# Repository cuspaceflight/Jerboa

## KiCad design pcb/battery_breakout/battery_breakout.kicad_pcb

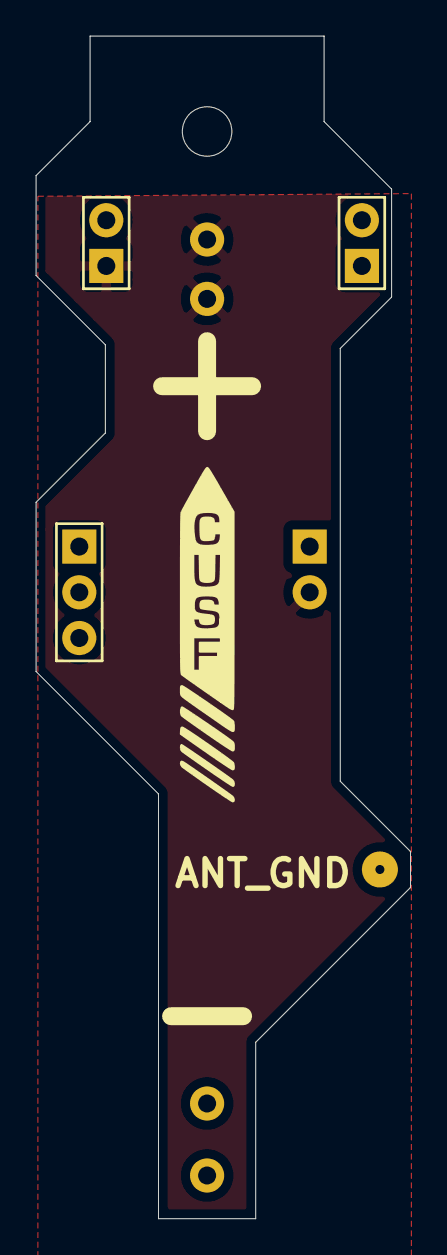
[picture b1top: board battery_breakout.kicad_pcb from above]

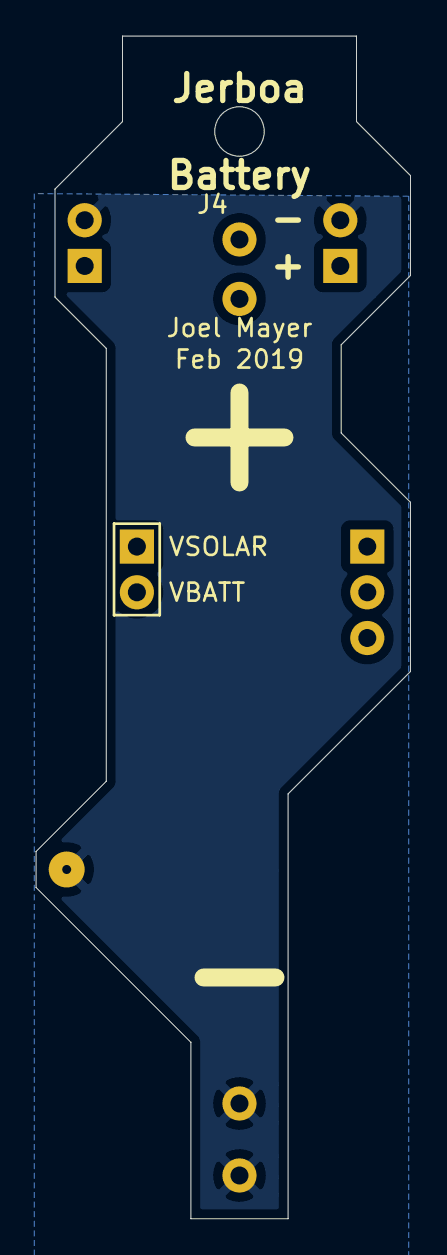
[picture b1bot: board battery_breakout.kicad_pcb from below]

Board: 2 copper layers, 20.8 x 65.7 mm, 5 parts (2 on the bottom side), 2 nets, no tracks yet.

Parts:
J1: BATTERY_HOLDER; AAA_battery_holder
J2, J3: CONN_01x02; SIL-254P-02
J4: BATTERY_HOLDER; AA_battery_holder
TP1: TESTPAD; ANT_GND_PASSTHROUGH

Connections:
/V_BATT: J1.1, J2.2, J3.1, J4.1
GND: J1.2, J3.2, J4.2, TP1.1

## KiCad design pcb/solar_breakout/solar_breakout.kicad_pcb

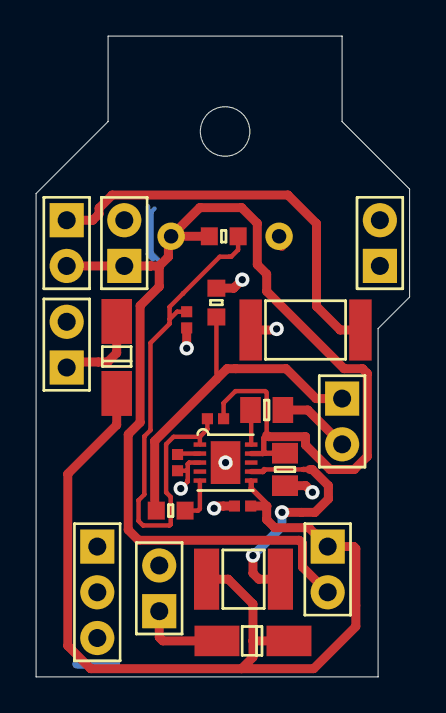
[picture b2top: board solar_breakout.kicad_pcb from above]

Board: 2 copper layers, 20.8 x 35.6 mm, 21 parts (1 on the bottom side), 12 nets.

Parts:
C1: 10n; 0603
C2: 10u; 0402
C3, C6: 1u; 0805
C4: 22p; 0402
C5: 4.7u; 0402
C7: 50; super_capacitor
D2, D3: SCHOTTKY; SMA_DIODE
IC1: LTC3105; DFN-10-EP-LT
J1, J2, J3, J4, J5, J6: CONN_01x02; SIL-254P-02
L1: 10u; 1812
R1: 76.8k; 0603
R2: 750k; 0603
R3: 510k; 0402
R4: 3.3; 2512

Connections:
/Array_1_+: D2.2, J1.1
/Array_2_+: D3.2, J2.1
/Cap_V: C4.2, C6.1, C7.2, IC1.9, J4.1, J5.2, J6.2, R2.1
/D_anode: C1.1, J3.1, R1.2
/Panel_V: C2.1, D2.1, D3.1, IC1.6, J5.1, L1.1
GND: C1.2, C2.2, C3.2, C5.2, C6.2, C7.1, IC1.3, IC1.EP, J1.2, J2.2, J3.2, J4.2, R3.2, R4.2
unnamed: C3.1, IC1.10
unnamed: C4.1, IC1.1, R2.2, R3.1
unnamed: C5.1, IC1.2
unnamed: IC1.5, R1.1
unnamed: IC1.7, L1.2
unnamed: J6.1, R4.1

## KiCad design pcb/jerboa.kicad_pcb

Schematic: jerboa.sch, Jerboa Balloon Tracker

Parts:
C5: 10uF; 0402; Farnell 2611904
C6, C8, C9, C10, C11: 100nF; 0402; Farnell 2533923
C7: 1uF; 0402; Farnell 1758879
D1: LED_GREEN; 0603-LED; Farnell 2575345
J1: CONN_01x02; SIL-254P-02; Farnell 1593458
J2: CONN_01x03; SIL-254P-03; Farnell 1593459
P1: SWD_TC; TC2030-NL
R6: 120; 0402; Farnell 2140682
R7, R8: 4k7; 0402; Farnell 2447187
R9: 1M; 0402; Farnell 2447127
U1: STM32L051K8U6; QFN-32-EP-ST; Farnell 2488323
X1: MOUNT; M2.5_HOLE
X2: CUSF_LOGO; cusf_logo

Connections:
3v3: C5.2, C6.2, C7.2, C8.2, C9.2, C11.2, J1.1, P1.1, R7.2, R8.2, U1.1, U1.5, U1.17; also elsewhere on the board
/BATT_V: U1.14; also elsewhere on the board
/FREQ_CTRL: U1.7; also elsewhere on the board
/GPS_EXTINT: U1.18; also elsewhere on the board
/GPS_~RESET: U1.21; also elsewhere on the board
/I2C_SCL: J2.2, R7.1, U1.29
/I2C_SDA: J2.3, R8.1, U1.30
/MCU_MISO: U1.12; also elsewhere on the board
/MCU_MOSI: U1.13; also elsewhere on the board
/MCU_SCK: U1.11; also elsewhere on the board
/MCU_SHUTDOWN_TO_RADIO: R9.1, U1.8; also elsewhere on the board
/MCU_nIRQ_TO_RADIO: U1.9; also elsewhere on the board
/NRST: C10.1, P1.3, U1.4
/RADIO_PWR_EN: U1.16; also elsewhere on the board
/RX_GPS_from_MCU: U1.20; also elsewhere on the board
/SI4460_NSS: U1.10; also elsewhere on the board
/SOLAR_CELL_VOLTAGE: U1.15; also elsewhere on the board
/SWCLK: P1.4, U1.24
/SWDIO: P1.2, U1.23
/TX_GPS_from_MCU: U1.19; also elsewhere on the board
/WSPR_ENABLE: J2.1, U1.28
GND: C5.1, C6.1, C7.1, C8.1, C9.1, C10.2, C11.1, D1.1, J1.2, P1.5, R9.2, U1.2, U1.31, U1.EP; also elsewhere on the board
unnamed: D1.2, R6.2
unnamed: R6.1, U1.25

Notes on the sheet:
16mA max current source
WSPR

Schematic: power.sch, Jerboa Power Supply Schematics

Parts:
C1, C12: 10uF; 0402; Farnell 2611904
C2: 470pF; 0402; Farnell 1327654
C3, C4: 1uF; 0402; Farnell 1758879
IC1: ADP1607; LFCSP-2x2; Farnell 2254940
J3, J4: CONN_01x02; SIL-254P-02; Farnell 1593458
L1: 2.2uH; 0806; Farnell 2520679
R1: 953k; 0402; Farnell 2141038
R2: 620k; 0402; Farnell 2073175
R3: 470k; 0402; Farnell 9239553
R4: 4k7; 0402; Farnell 2447187
U2: FDC6329L; SuperSOT-6; Farnell 1652469
U3: NCP4620; SC-70-5; Farnell 2464259

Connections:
1v8: C4.1, U3.4; also elsewhere on the board
3v3: C1.1, IC1.6, R1.1, R3.2, U2.4; also elsewhere on the board
/BATT_V: J4.2; also elsewhere on the board
/RADIO_PWR_EN: U2.5; also elsewhere on the board
/SOLAR_CELL_VOLTAGE: J4.1; also elsewhere on the board
GND: C1.2, C3.1, C4.2, C12.2, IC1.4, IC1.7, J3.2, R2.2, R4.2, U3.3; also elsewhere on the board
unnamed: C2.1, R3.1, U2.6
unnamed: C12.1, IC1.1, IC1.2, J3.1, L1.1
unnamed: IC1.3, R1.2, R2.1
unnamed: IC1.5, L1.2
unnamed: R4.1, U2.1

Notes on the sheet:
Analog in from solar cells
Battery/capacitor input
Boost Regulator
Radio Power Load Switch
1V8 Regulator

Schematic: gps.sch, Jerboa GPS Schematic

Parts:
AE1: Antenna_Chip; 1575AT43A0040E; Digikey 712-1003-2-ND
C16: 100nF; 0402; Farnell 2533923
IC2: MAX-M8Q

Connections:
3v3: C16.1, IC2.6, IC2.7, IC2.8; also elsewhere on the board
/GPS_EXTINT: IC2.5; also elsewhere on the board
/GPS_~RESET: IC2.9; also elsewhere on the board
/RX_GPS_from_MCU: IC2.2; also elsewhere on the board
/TX_GPS_from_MCU: IC2.3; also elsewhere on the board
GND: C16.2, IC2.1, IC2.10, IC2.12; also elsewhere on the board
unnamed: AE1.2, IC2.11

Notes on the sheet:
GPS

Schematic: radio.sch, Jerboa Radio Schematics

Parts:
C13, C20: 10nF; 0402; Farnell 2332514
C14, C17: 100pF; 0402; Farnell 2496792
C18: 100nF; 0402; Farnell 2533923
C19: 1uF; 0402; Farnell 1758879
C21, C28, C31: 18pF; 0402; Farnell 2522556
C23: 39pF; 0402; Farnell 2524782
C25, C30: 8.2pF; 0402; Farnell 1865418
C26: 6.8pF; 0402; Farnell 2310317
C27: 15pF; 0402; Farnell 2520723
C29: 3pF; 0402; Farnell 1758933
C32: 2pF; 0402; Farnell 1758932
C33: 470pF; 0402; Farnell 1327654
C34, C35: C; 0603
D2, D3: ESD_DIODE; 0402; Farnell 2368169
IC3: Si4460; QFN-20-EP-SI; Farnell 2462635
IC4: BGS12AL7; TSLP7-4; Farnell 2480594
L2: 250nH; 0603; Mouser 81-LQW18ANR22J8ZD
L3: 100nH; 0402; Farnell 1762632
L4: 56nH; 0603; Farnell 1711807
L6: 22nH; 0402; Farnell 2840114
L7, L10: 18nH; 0402; Farnell 1762622
L11: 68nH; 0402; Farnell 1669641
L12: 47nH; 0402; Farnell 1343090
L13, L14: L; 0603
P2: 434MHz; GND_PLANE_ANT
P3: 144MHz; GND_PLANE_ANT
TP1: TESTPAD; ANT_GND_PASSTHROUGH
Y1: TCXO; TG-5006CG; Farnell 2405785

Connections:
1v8: C13.2, Y1.4; also elsewhere on the board
/FREQ_CTRL: IC4.6; also elsewhere on the board
/MCU_MISO: IC3.13; also elsewhere on the board
/MCU_MOSI: IC3.14; also elsewhere on the board
/MCU_SCK: IC3.12; also elsewhere on the board
/MCU_SHUTDOWN_TO_RADIO: IC3.1; also elsewhere on the board
/MCU_nIRQ_TO_RADIO: IC3.11; also elsewhere on the board
/SI4460_NSS: IC3.15; also elsewhere on the board
/radio/RADIO_TX_144: C23.1, IC4.3
/radio/RADIO_TX_434: C21.1, IC4.1
GND: C13.1, C17.1, C18.1, C19.1, C25.2, C26.2, C27.2, C28.2, C30.2, C31.2, C34.2, C35.2, D2.2, D3.2, IC3.2, IC3.3, IC3.18, IC3.EP, IC4.2, IC4.EP, P2.2, P3.2, TP1.1, Y1.2; also elsewhere on the board
unnamed: C14.1, Y1.3
unnamed: C14.2, IC3.17
unnamed: C20.1, IC3.4, L2.2
unnamed: C20.2, IC4.5
unnamed: C21.2, L4.1
unnamed: C23.2, L6.1
unnamed: C25.1, L4.2, L7.1
unnamed: C26.1, L3.1, L6.2
unnamed: C27.1, L7.2, L10.1
unnamed: C28.1, C29.1, L3.2, L11.1
unnamed: C29.2, C31.1, C32.1, L11.2, L12.1
unnamed: C30.1, C35.1, L10.2, L14.1
unnamed: C32.2, C33.1, L12.2
unnamed: C33.2, C34.1, L13.1
unnamed: D2.1, L14.2, P2.1
unnamed: D3.1, L13.2, P3.1

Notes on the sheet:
Si4460
Si4460 Antenna Matching - 169MHz
https://www.silabs.com/documents/public/application-notes/AN627.pdf 169MHz matching (Direct Tie CLE)
Antenna GND plane pass through
Si4460 Antenna Matching - 434MHz
https://www.silabs.com/documents/public/application-notes/AN627.pdf 434MHz matching (Split Tx CLE)
Large
See also http://tt7hab.blogspot.com/2017/05/the-tt7f-v15-revision.html
Zload = (0.2815)/(2 * pi * 434MHz * 1.25pF) * e^j * 49.0524degrees Zload = 54.12 + 62.38j ohm at 434MHz
Vdd = sqrt(0.02/ (2*pi^2 * 434MHz * 1.25pF) ) = 1.37V Idd = 2 * pi^2 * 434MHz * 1.25pF * Vdd = 0.0146A Rdc = (3.3V - Vdd) / Idd = 132.1ohm (set PA_PWR_LVL register appropriately)
Impedance matching (match to 50ohms as filter matches to Zload) Values unknown
Low pass filter
LC resonant tank
Zload = (0.2815)/(2 * pi * 144MHz * 1.25pF) * e^j * 49.0524degrees Zload = 163.1 + 188.0j ohm at 144MHz
Vdd = sqrt(0.01/ (2*pi^2 * 144MHz * 1.25pF) ) = 1.68V Idd = 2 * pi^2 * 144MHz * 1.25pF * Vdd = 0.00596A Rdc = (3.3V - Vdd) / Idd = 272.2ohm (set PA_PWR_LVL register appropriately)
Inductor sets DC bias, switch can only pass RF (not DC)

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
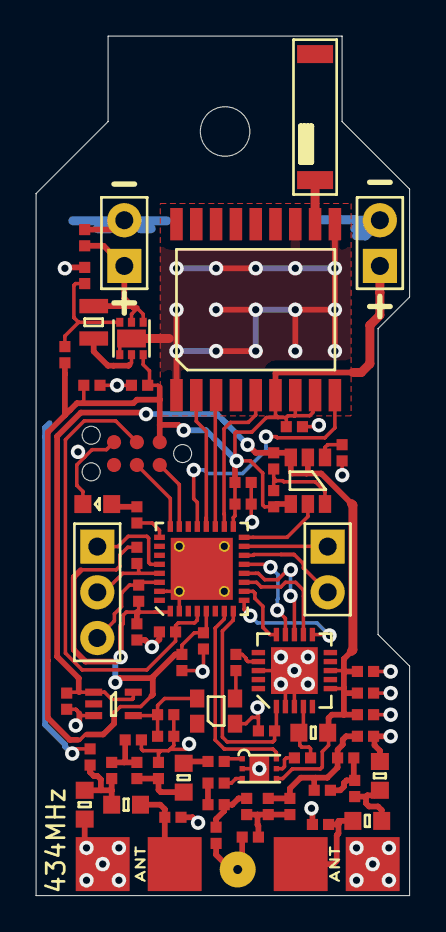
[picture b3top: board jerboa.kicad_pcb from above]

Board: 2 copper layers, 20.8 x 47.7 mm, 73 parts (1 on the bottom side), 50 nets.

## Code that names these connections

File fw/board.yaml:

name: Jerboa
lsefreq: 0
hsefreq: 0
voltage: 3.3
mcutype: STM32L051xx
other:
    STM32_HSE_BYPASS: ~
    STM32_LSEDRV: (3U << 11U) 
default: input, opendrain, startlow, pulldown, lowspeed
pins:
    freq_ctrl:  pa1, output, pushpull, starthigh, pullup
    radio_sdn:  pa2, output, pushpull, floating
    radio_nirq: pa3, output, pushpull, starthigh, pullup
    radio_nss:  pa4, output, pushpull, starthigh, pullup, highspeed
    mcu_sck:    pa5, af0, pushpull, starthigh, pullup, highspeed
    mcu_miso:   pa6, af0, pushpull, starthigh, pullup, highspeed
    mcu_mosi:   pa7, af0, pushpull, starthigh, pullup, highspeed
    gps_extint: pa8, output, pushpull, startlow, pulldown
    gps_tx:     pa9, af4, pushpull, starthigh, pullup, highspeed
    gps_rx:    pa10, af4, pushpull, starthigh, pullup, highspeed
    gps_nrst:  pa11, output, pushpull, starthigh, pullup
    swdio:     pa13, af0, pushpull, starthigh, pullup, highspeed
    swclk:     pa14, af0, pushpull, starthigh, pulldown, highspeed
    led:       pa15, output, pushpull
    
    batt_v:       pb0, analog, floating
    solar_cell_v: pb1, analog, floating
    radio_pwr_en: pb2, output, pushpull, startlow, pulldown
    wspr_en:      pb5, output, pushpull, startlow, pulldown
    i2c_scl:      pb6, af1, opendrain, starthigh, floating, highspeed
    i2c_sda:      pb7, af1, opendrain, starthigh, floating, highspeed

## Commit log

2017-12-07 Add submodules
2017-12-08 Set up KiCad project with relative paths to agg-kicad
2017-12-18 Add subsheets for schematic and create symbol for STM32L051K8U6
2017-12-23 Some work on mcu circuitry
2017-12-25 Begin gps schematic, assuming dcdc converter used
2018-01-24 Add some component values
2018-01-24 Added radio circuit
2018-01-24 Forgot to save
2018-01-28 Schematic almost done.
2018-01-28 Added shutdown and interrupt control for Radio
2018-01-28 Attempt to fix symbol library problems from old kicad version
2018-01-29 Some schematic work, create a todo with ideas for power supply components
2018-01-31 Add TPS61025 switching regulator to schematic
2018-01-31 Draft a PCB for the battery breakout board
2018-01-31 Round right angled corners on board
2018-02-01 Update todo
2018-02-02 Update todo again with wspr/clocking todo
2018-02-08 Add solar breakout
2018-02-09 Work on solar breakout board
2018-02-10 Create some more schematic symbols and footprints
2018-02-15 Work on schematic
2018-02-18 Add wspr breakout board and reorganise sub project libraries
2018-02-18 Update wspr breakout footprints
2018-02-18 Use schottky diode in solar breakout, compensate with extra series solar panels
2018-02-25 Update clock input for clock buffer
2018-05-19 Update submodules
2018-06-11 Add chip antenna to GPS schematic
2018-06-11 WIP: create and add componenents for the micrf rtty radio, also do some work on schematic
2018-06-12 Fix paths in sym lib table
2018-06-12 Finish schematic, generate first BOM
2018-06-12 Fill in schematic title blocks
2018-06-12 Remove *-cache.lib and *.bak files
2018-06-12 Fix footprint name error (agg:0805-L does not exist)
2018-06-12 WIP: begin board layout
2018-06-13 Redo si4460 matching for 169MHz
2018-06-13 Update BOM
2018-06-13 WIP: work on pcb, use guitar wire ground plane antenna and remove rx matching on si4460 as there is nothing to receive
2018-06-14 WIP: more pcb layout, add rx stuff again
2018-06-14 WIP: add clock circuitry to pcb
2018-06-14 WIP: attempt at routing spi
2018-06-15 WIP: more pcb layout
2018-06-15 Stash dual radio version in separate branch
2018-06-15 Schematic (and some pcb) using si4460 for both 144MHz and 434MHz
2018-06-16 Add footprints for 50ohm matching of antennas, work on schematic & pcb
2018-06-17 More PCB layout
2018-06-18 More pcb routing
2018-06-18 Restart routing, attempt to preserve ground plane this time
2018-07-05 Use relative path for submodules (should work for ssh and https)
2018-07-08 WIP: Begin making schematic changes - replace boost regulator with ADP1607 and add load switch for radio power
2018-07-09 Finish redoing clock circuitry
2018-07-09 Begin routing pcb (again)
2018-07-09 WIP: rough component layout for PCB
2018-07-10 WIP: More PCB routing
2018-07-10 WIP: begin to place radio matching circuit on PCB
2018-07-11 WIP: First attempt at routing 144MHz matching network
2018-07-14 Even more PCB routing
2018-07-15 Finish first iteration of Jerboa PCB
2018-07-22 Begin filling in firmware template
2018-07-23 added panel
2018-07-23 added panel zip
2018-07-23 Attempt to get firmware to compile using an example for STM32L052xx from Chibios v18.2.0, use CUSF fork to branch off from this ChibiOS commit
2018-07-24 Switch to basing changes on ChibiOS stable release 18.2.x
2018-07-24 Firmware now builds
2018-07-24 Use ChibiOS repository again
2018-07-24 Add pdfs
2018-07-25 Firmware: add top level state machine and some TODOs
2018-09-27 Update .gitignore to ignore eclipse project directories
2018-09-28 Use HarkonenBade gen_board.h and chibios master branch to create board.h and build firmware
2018-09-28 Update CHibiOS configuration, ready for firmware development
2018-10-06 Update ChibiOS and chconf.h, now supports pipes
2018-10-06 Blink example
2018-10-06 added GDB_PORT argument for Makefile
2018-10-06 added radio driver, greg got a mcu with no memory...
2018-10-06 Tidy up Makefile
2018-10-06 Add test code to enter low power standby mode periodically using the RTC wakeup
2018-10-08 added gps code
2018-10-14 Make some changes to USART pin config and gps setup during testing
2018-10-14 Forgot to save merged file
2018-10-14 removed ldpc codes
2018-12-08 Initial symbol fields
2018-12-08 Tidy some schematic errors
2018-12-08 Fix some symbol fields
2019-01-02 Fill in more symbol fields
2019-01-20 Add values for super capacitor
2019-01-20 Make super capacitor footprint
2019-01-20 Fix lowercase jerboa.pretty
2019-01-20 Improve footprint of super capacitor
2019-01-26 Check component footprints, Farnell numbers etc. Make some changes
2019-01-27 Begin solar pcb
2019-01-27 Set up design rules
2019-01-29 Begin firmware for habpack packet printing
2019-01-31 Add functions to form UKHAS style telemetry strings
2019-02-01 Modify GPS driver so that PVT messages can be polled, first attempt at UKHAS style telemetry string generation using chsnprintf
2019-02-02 First draft of PCB
2019-02-03 Fix some stuff on pcb (from the Dyson Centre)
2019-02-03 add solar iv graph
2019-02-03 Work on pcb
2019-02-03 Add more stuff to pcb
2019-02-04 Update pcb
2019-02-17 Do checks on PCB and add edge cuts
2019-02-18 Fix some stuff with the PCB
2019-02-18 Make the baord smaller and fix power lines
2019-02-18 Fix some traces and move connections closer to edge
2019-02-19 Improve routing and change resistor
2019-02-19 Forgot to save file
2019-02-19 Fix small changes to both boards
2019-02-19 Make some last minute changes to PCBs before sending off for manufacture
2019-02-19 Add gerbers
2019-07-14 Add dummy rtty driver (toggle LED instead of FSK)
2019-07-14 UNTESTED: add to GPS config so that extint can wake/sleep GPS
2019-07-14 Fix bugs
2019-07-14 radio driver integrated
2019-07-20 Fix more bugs
2019-07-20 Use GPT for RTTY timings
2019-07-20 Add RF switch control to firmware
2019-07-20 UNTESTED: add ADC battery voltage measurement to RTTY string
2019-07-29 Fix bug: properly stop gpt after radio transmission
2019-07-31 Reduce carrier shift to 850Hz and tidy up stop bit comments
2019-08-03 Fix some bugs and use standard snprintf to print lat lon
2019-08-03 Add watchdog timer and turn off LED for flight
